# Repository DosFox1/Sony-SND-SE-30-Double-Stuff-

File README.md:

# Sony-SND-SE-30-Double-Stuff
BETA - A replacement for the Sony SND IC (part number 343-0045-A), specifically designed for the SE/30.
This design is a duplication of the previous Sony SND SMD version, but literally copied twice to fit two Sony SNDs onto the board without the DRC yelling at me.

# So What Is It?
This is quite literally the same design as before, with the same improvement of not needing the -12V rail. 
However, due to the board constraints of the SE/30, two of my SMD boards will not fit - at least easily. 
So this design just adds a second SND replacement so the DRC doesn't yell at me. 

It's all common jellybean parts, so nothing hyper specific is needed.

**Please note that -12V will need to be tapped from somewhere on the board, otherwise the audio doesn't work.**

**Also the 27R Pullup resistor at R11 on the logic board needs to be removed, otherwise POR doesn't work!**

The original SMD Design is here:
https://github.com/DosFox1/Sony-SND-SMT-Replacement

And the very original THT design is here:
https://github.com/DosFox1/Sony-SND-THT-Replacement

**Please Also Note That This Is Completely Untested, Build At Your Own Risk**

# Bill Of Materials:

```blocks
Part     Value          Device                       Package  Library                Sheet

C1       100n 16V       100N_CAP_0603                C0603    Capacitors SMD         1
C2       100n 16V       100N_CAP_0603                C0603    Capacitors SMD         1
C3       100n 16V       100N_CAP_0603                C0603    Capacitors SMD         1
C4       100n 16V       100N_CAP_0603                C0603    Capacitors SMD         1
C5       1u 16V         1U_CAP_0603                  C0603    Capacitors SMD         1
C6       100n 16V       100N_CAP_0603                C0603    Capacitors SMD         1
C7       470p           100P_CAP_0603                C0603    Capacitors SMD         1
C8       1n 50V         10N_CAP_0603                 C0603    Capacitors SMD         1
C9       100n 16V       100N_CAP_0603                C0603    Capacitors SMD         1
C10      100n 16V       100N_CAP_0603                C0603    Capacitors SMD         1
C11      220p           100P_CAP_0603                C0603    Capacitors SMD         1
C12      100n 16V       100N_CAP_0603                C0603    Capacitors SMD         1
C13      100n 16V       100N_CAP_0603                C0603    Capacitors SMD         1
C14      100n 16V       100N_CAP_0603                C0603    Capacitors SMD         1
C15      100n 16V       100N_CAP_0603                C0603    Capacitors SMD         1
C16      100n 16V       100N_CAP_0603                C0603    Capacitors SMD         1
C17      470p           100P_CAP_0603                C0603    Capacitors SMD         1
C18      1n 50V         10N_CAP_0603                 C0603    Capacitors SMD         1
C19      100n 16V       100N_CAP_0603                C0603    Capacitors SMD         1
C20      100n 16V       100N_CAP_0603                C0603    Capacitors SMD         1
C21      220p           100P_CAP_0603                C0603    Capacitors SMD         1
C22      100n 16V       100N_CAP_0603                C0603    Capacitors SMD         1
C23      1u 16V         1U_CAP_0603                  C0603    Capacitors SMD         1
C24      100n 16V       100N_CAP_0603                C0603    Capacitors SMD         1
D1       5.1V           DIODE-ZENER-MMSZ5232BS       SOD-123  SparkFun-DiscreteSemi  1
D2       5.1V           DIODE-ZENER-MMSZ5232BS       SOD-123  SparkFun-DiscreteSemi  1
IC1      TL072          OPAMP-DUALU                  SO08     SparkFun-IC-Amplifiers 1
IC2      4016D          4016D                        SO14     40xx                   1
IC3      NE555DRG4      555_SOIC8                    SOIC8    ICs                    1
IC4      74LVC1G06DBV   74LVC1G06DBV                 SOT23-5  74xx-little-us         1
IC5      Turned Pins    SND Turned Pins              DIP16    Pins                   1
IC6      4016D          4016D                        SO14     40xx                   1
IC7      Turned Pins    SND Turned Pins              DIP16    ICs                    1
IC8      74LVC1G06DBV   74LVC1G06DBV                 SOT23-5  74xx-little-us         1
IC9      NE555DRG4      555_SOIC8                    SOIC8    Pins                   1
IC10     TL072          OPAMP-DUALU                  SO08     SparkFun-IC-Amplifiers 1
Q1       MMBT3906       TRANS_PNP-PMBT3906|MMBT3906L SOT23-3  SparkFun-DiscreteSemi  1
Q2       MMBT3904       TRANS_NPN-MMBT2222AL         SOT23-3  SparkFun-DiscreteSemi  1
Q3       MMBT3906       TRANS_PNP-PMBT3906|MMBT3906L SOT23-3  SparkFun-DiscreteSemi  1
Q4       MMBT3904       TRANS_NPN-MMBT2222AL         SOT23-3  SparkFun-DiscreteSemi  1
R1       1M             GENERIC_RESISTOR_0603        R0603    Resistors SMD          1
R2       1M             GENERIC_RESISTOR_0603        R0603    Resistors SMD          1
R3       6K8            GENERIC_RESISTOR_0603        R0603    Resistors SMD          1
R4       47K            47K_RESISTOR                 R0603    Resistors SMD          1
R5       1k             1K_RESISTOR_0603             R0603    Resistors SMD          1
R6       47K            47K_RESISTOR                 R0603    Resistors SMD          1
R7       68K            GENERIC_RESISTOR_0603        R0603    Resistors SMD          1
R8       150K           GENERIC_RESISTOR_0603        R0603    Resistors SMD          1
R9       470K           GENERIC_RESISTOR_0603        R0603    Resistors SMD          1
R10      470K           GENERIC_RESISTOR_0603        R0603    Resistors SMD          1
R11      200K           GENERIC_RESISTOR_0603        R0603    Resistors SMD          1
R12      150R           150R_RESISTOR_0603           R0603    Resistors SMD          1
R13      47K            47K_RESISTOR                 R0603    Resistors SMD          1
R14      47K            47K_RESISTOR                 R0603    Resistors SMD          1
R15      1M             GENERIC_RESISTOR_0603        R0603    Resistors SMD          1
R16      1M             GENERIC_RESISTOR_0603        R0603    Resistors SMD          1
R17      1k             1K_RESISTOR_0603             R0603    Resistors SMD          1
R18      6K8            GENERIC_RESISTOR_0603        R0603    Resistors SMD          1
R19      68K            GENERIC_RESISTOR_0603        R0603    Resistors SMD          1
R20      150K           GENERIC_RESISTOR_0603        R0603    Resistors SMD          1
R21      470K           GENERIC_RESISTOR_0603        R0603    Resistors SMD          1
R22      470K           GENERIC_RESISTOR_0603        R0603    Resistors SMD          1
R23      200K           GENERIC_RESISTOR_0603        R0603    Resistors SMD          1
R24      150R           150R_RESISTOR_0603           R0603    Resistors SMD          1

```

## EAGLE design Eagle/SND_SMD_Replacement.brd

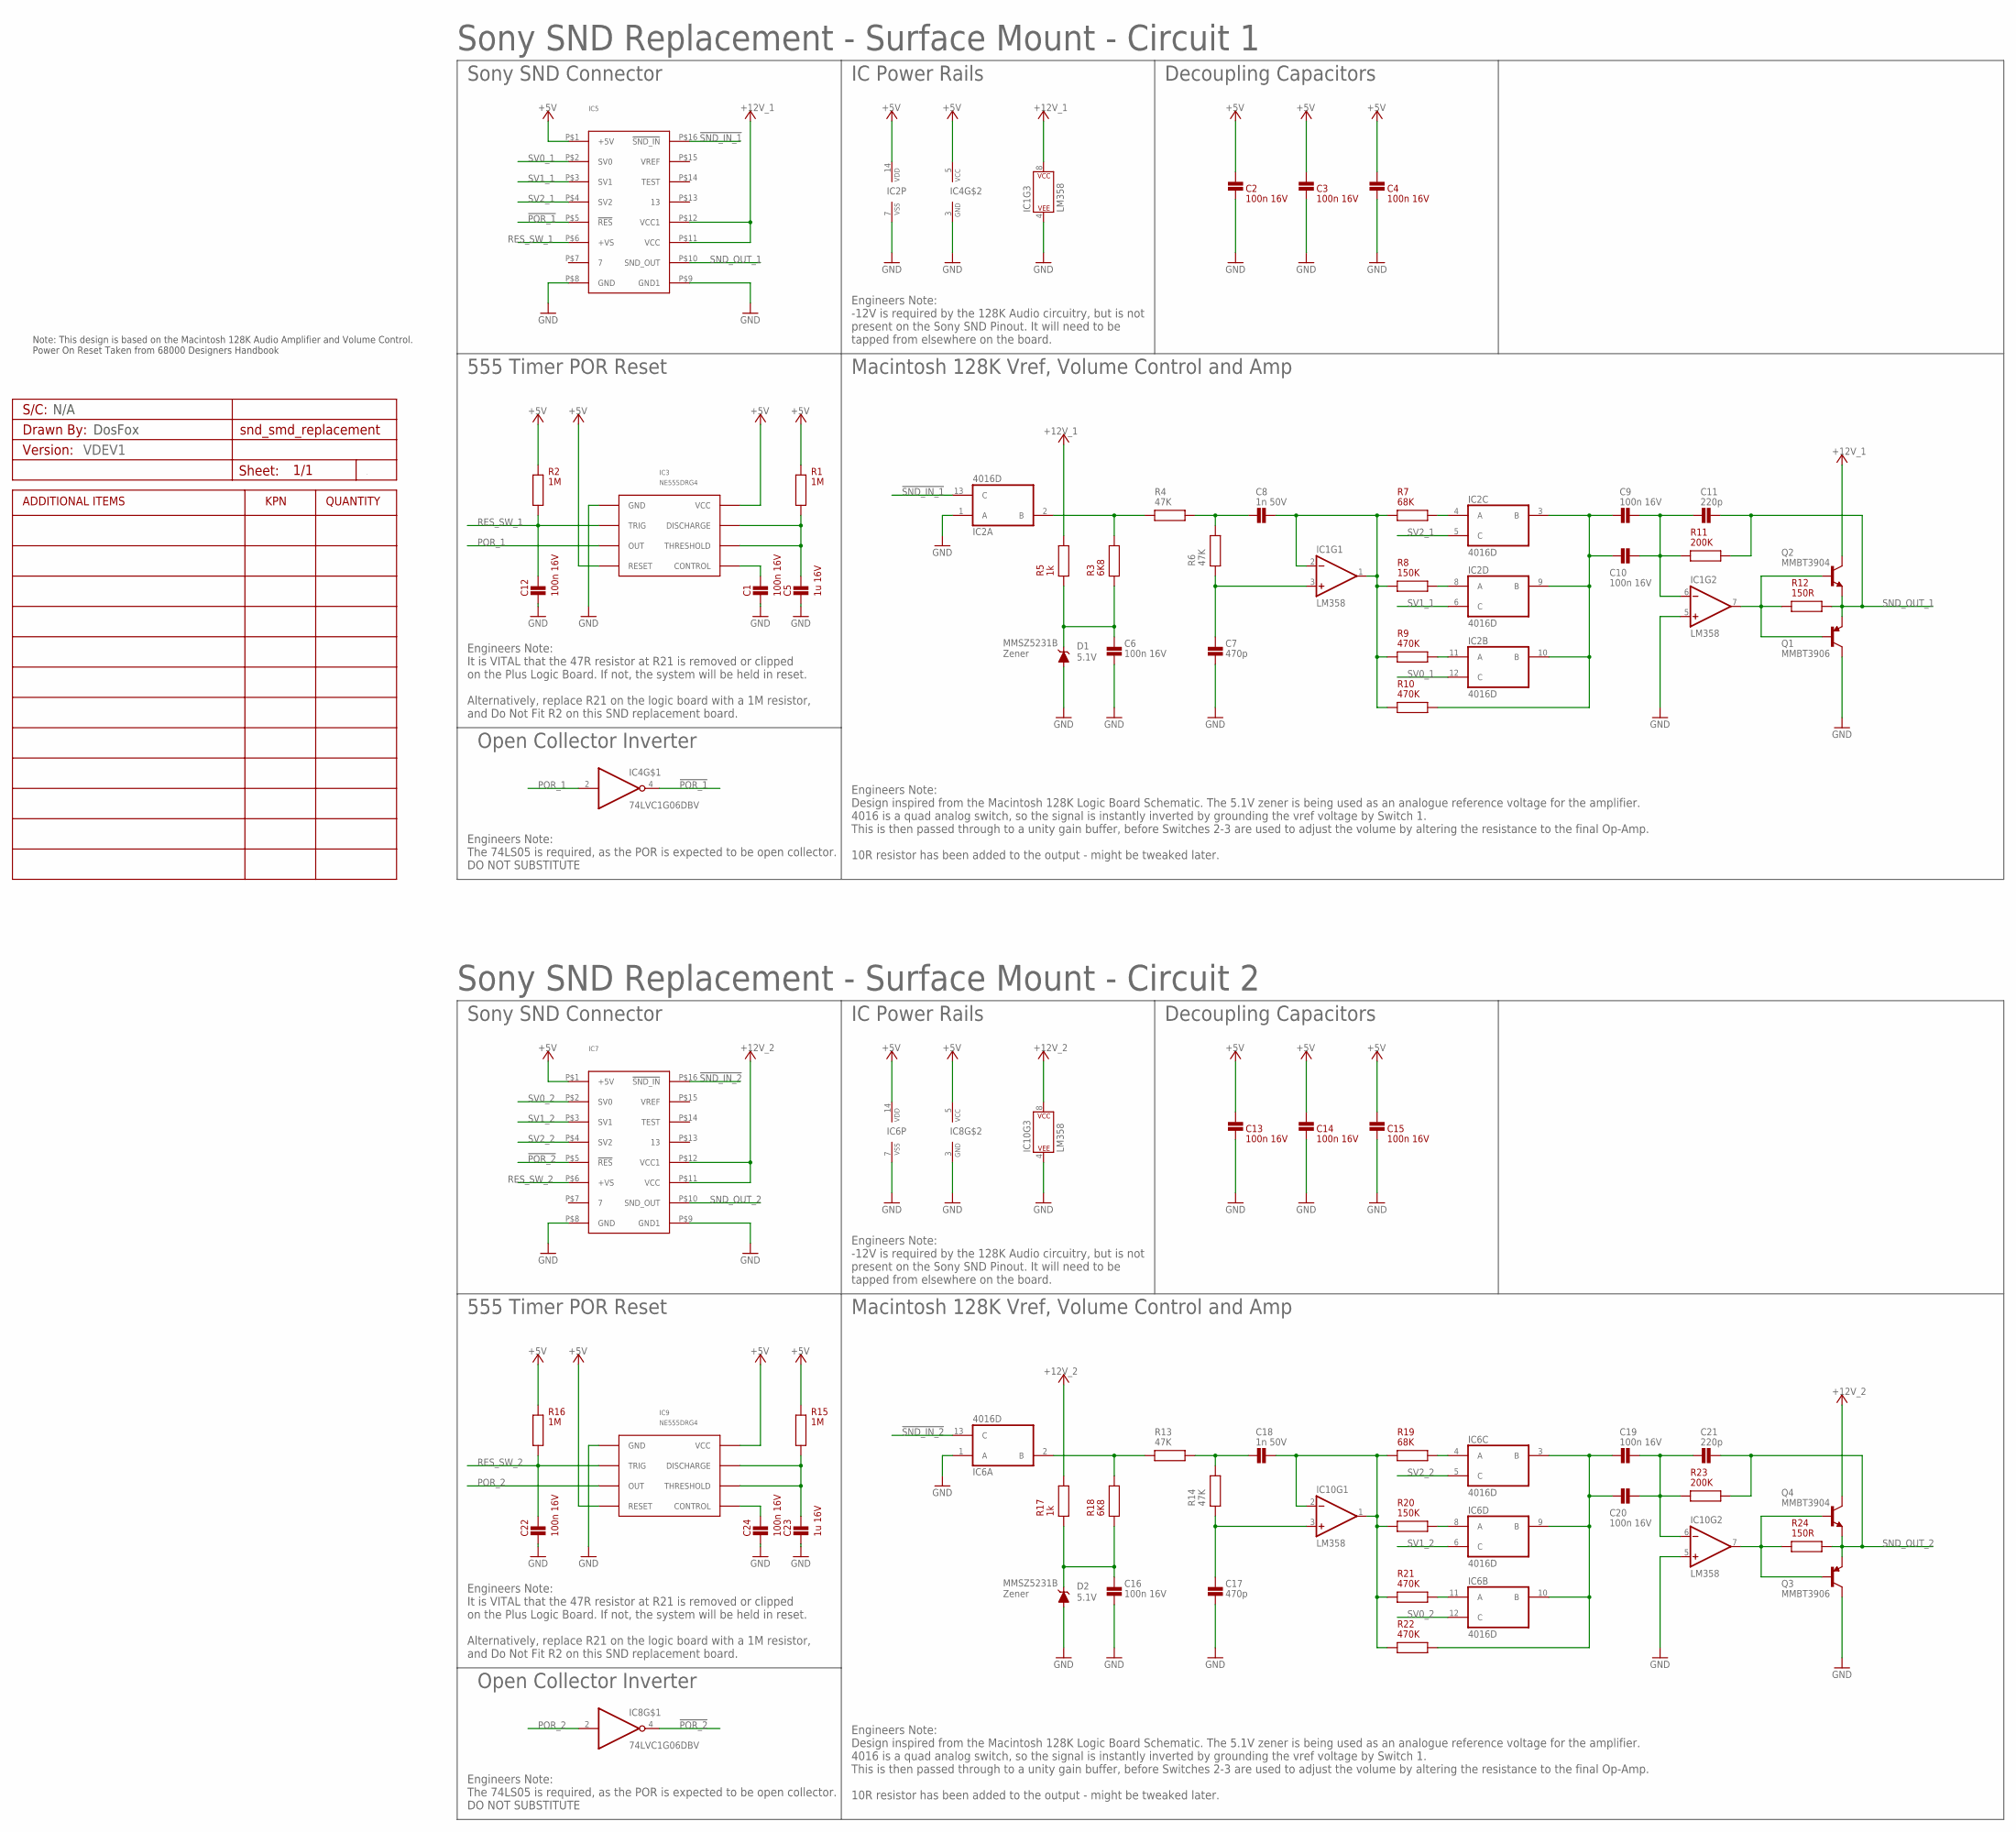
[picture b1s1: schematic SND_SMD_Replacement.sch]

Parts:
A1: VDEV1; PCB_CUSTOM_DETAILS
C1, C2, C3, C4, C6, C9, C10, C12, C13, C14, C15, C16, C19, C20, C22, C24: 100n 16V; C0603
C5, C23: 1u 16V; C0603
C7, C17: 470p; C0603
C8, C18: 1n 50V; C0603
C11, C21: 220p; C0603
D1, D2: 5.1V; SOD-323
IC1, IC10: LM358; SO08
IC2, IC6: 4016D; SO14
IC3, IC9: NE555DRG4; SOIC8
IC4, IC8: 74LVC1G06DBV; SOT23-5
IC5, IC7: SND; DIP16
Q1, Q3: MMBT3906; SOT23-3
Q2, Q4: MMBT3904; SOT23-3
R1, R2, R15, R16: 1M; R0603
R3, R18: 6K8; R0603
R4, R6, R13, R14: 47K; R0603
R5, R17: 1k; R0603
R7, R19: 68K; R0603
R8, R20: 150K; R0603
R9, R10, R21, R22: 470K; R0603
R11, R23: 200K; R0603
R12, R24: 150R; R0603

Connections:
!POR_1: IC4.4 (O), IC5.P$5 (!RES)
!POR_2: IC7.P$5 (!RES), IC8.4 (O)
!SND_IN_1: IC2.13 (C), IC5.P$16 (!SND_IN)
!SND_IN_2: IC6.13 (C), IC7.P$16 (!SND_IN)
+5V: C2.2, C3.2, C4.2, C13.2, C14.2, C15.2, IC2.14 (VDD), IC3.P$4 (RESET), IC3.P$8 (VCC), IC4.5 (VCC), IC5.P$1 (+5V), IC6.14 (VDD), IC7.P$1 (+5V), IC8.5 (VCC), IC9.P$4 (RESET), IC9.P$8 (VCC), R1.2, R2.2, R15.2, R16.2
+12V_1: IC1.8 (P$V+), IC5.P$11 (VCC), IC5.P$12 (VCC1), Q2.3 (C), R5.2
+12V_2: IC7.P$11 (VCC), IC7.P$12 (VCC1), IC10.8 (P$V+), Q4.3 (C), R17.2
GND: C1.1, C2.1, C3.1, C4.1, C5.1, C6.1, C7.1, C12.1, C13.1, C14.1, C15.1, C16.1, C17.1, C22.1, C23.1, C24.1, D1.A, D2.A, IC1.4 (P$V-), IC1.5 (+IN), IC2.1 (A), IC2.7 (VSS), IC3.P$1 (GND), IC4.3 (GND), IC5.P$8 (GND), IC5.P$9 (GND1), IC6.1 (A), IC6.7 (VSS), IC7.P$8 (GND), IC7.P$9 (GND1), IC8.3 (GND), IC9.P$1 (GND), IC10.4 (P$V-), IC10.5 (+IN), Q1.3 (C), Q3.3 (C)
unnamed: IC2.2 (B), R3.2, R4.1
unnamed: C19.1, C20.1, IC6.3 (B), IC6.9 (B), IC6.10 (B), R22.2
unnamed: C9.1, C10.1, IC2.3 (B), IC2.9 (B), IC2.10 (B), R10.2
unnamed: C8.1, R4.2, R6.2
unnamed: C6.2, D1.C, R3.1, R5.1
unnamed: C7.2, IC1.3 (+IN), R6.1
unnamed: IC2.4 (A), R7.2
unnamed: IC2.8 (A), R8.2
unnamed: IC2.11 (A), R9.2
unnamed: C9.2, C10.2, C11.1, IC1.6 (-IN), R11.1
unnamed: C5.2, IC3.P$6 (THRESHOLD), IC3.P$7 (DISCHARGE), R1.1
unnamed: C8.2, IC1.1 (OUT), IC1.2 (-IN), R7.1, R8.1, R9.1, R10.1
unnamed: IC6.2 (B), R13.1, R18.2
unnamed: C18.1, R13.2, R14.2
unnamed: IC1.7 (OUT), Q1.1 (B), Q2.1 (B), R12.1
unnamed: C16.2, D2.C, R17.1, R18.1
unnamed: C1.2, IC3.P$5 (CONTROL)
unnamed: C17.2, IC10.3 (+IN), R14.1
unnamed: IC6.4 (A), R19.2
unnamed: IC6.8 (A), R20.2
unnamed: IC6.11 (A), R21.2
unnamed: C19.2, C20.2, C21.1, IC10.6 (-IN), R23.1
unnamed: IC10.7 (OUT), Q3.1 (B), Q4.1 (B), R24.1
unnamed: C18.2, IC10.1 (OUT), IC10.2 (-IN), R19.1, R20.1, R21.1, R22.1
unnamed: C23.2, IC9.P$6 (THRESHOLD), IC9.P$7 (DISCHARGE), R15.1
unnamed: C24.2, IC9.P$5 (CONTROL)
POR_1: IC3.P$3 (OUT), IC4.2 (I)
POR_2: IC8.2 (I), IC9.P$3 (OUT)
RES_SW_1: C12.2, IC3.P$2 (TRIG), IC5.P$6 (+VS), R2.1
RES_SW_2: C22.2, IC7.P$6 (+VS), IC9.P$2 (TRIG), R16.1
SND_OUT_1: C11.2, IC5.P$10 (SND_OUT), Q1.2 (E), Q2.2 (E), R11.2, R12.2
SND_OUT_2: C21.2, IC7.P$10 (SND_OUT), Q3.2 (E), Q4.2 (E), R23.2, R24.2
SV0_1: IC2.12 (C), IC5.P$2 (SV0)
SV0_2: IC6.12 (C), IC7.P$2 (SV0)
SV1_1: IC2.6 (C), IC5.P$3 (SV1)
SV1_2: IC6.6 (C), IC7.P$3 (SV1)
SV2_1: IC2.5 (C), IC5.P$4 (SV2)
SV2_2: IC6.5 (C), IC7.P$4 (SV2)

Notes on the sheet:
Note: This design is based on the Macintosh 128K Audio Amplifier and Volume Control. Power On Reset Taken from 68000 Designers Handbook
DosFox
N/A
MMSZ5231B Zener
Sony SND Replacement - Surface Mount - Circuit 1
Sony SND Connector
IC Power Rails
Decoupling Capacitors
555 Timer POR Reset
Open Collector Inverter
Macintosh 128K Vref, Volume Control and Amp
Engineers Note: Design inspired from the Macintosh 128K Logic Board Schematic. The 5.1V zener is being used as an analogue reference voltage for the amplifier. 4016 is a quad analog switch, so the signal is instantly inverted by grounding the vref voltage by Switch 1. This is then passed through to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
Engineers Note: It is VITAL that the 47R resistor at R21 is removed or clipped on the Plus Logic Board. If not, the system will be held in reset. Alternatively, replace R21 on the logic board with a 1M resistor, and Do Not Fit R2 on this SND replacement board.
Engineers Note: The 74LS05 is required, as the POR is expected to be open collector. DO NOT SUBSTITUTE
Engineers Note: -12V is required by the 128K Audio circuitry, but is not present on the Sony SND Pinout. It will need to be tapped from elsewhere on the board.
Sony SND Replacement - Surface Mount - Circuit 2

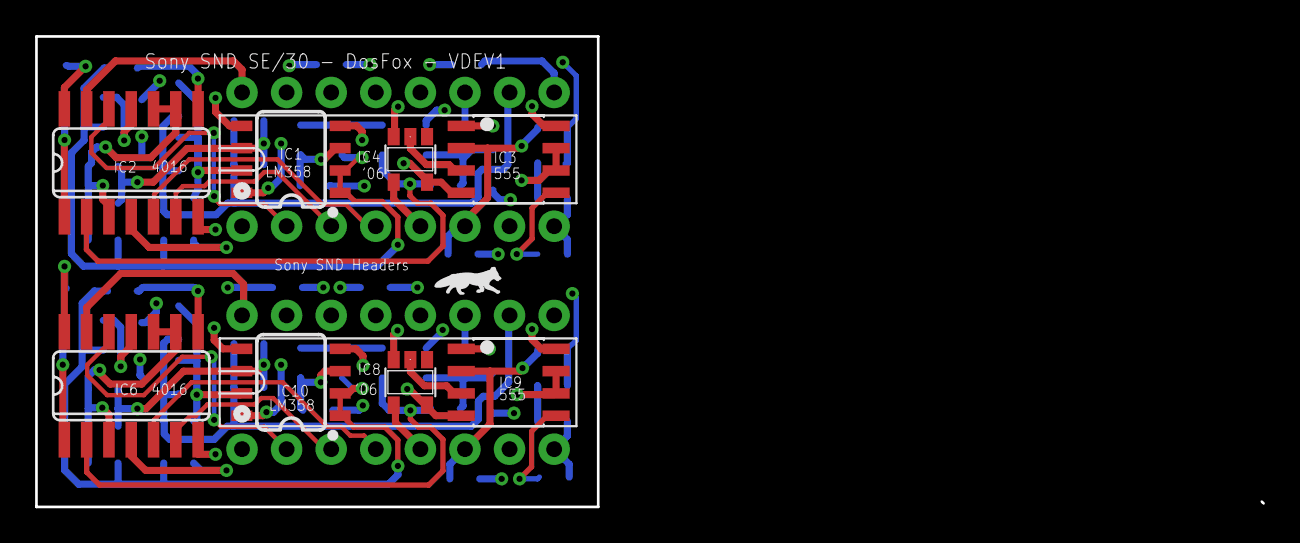
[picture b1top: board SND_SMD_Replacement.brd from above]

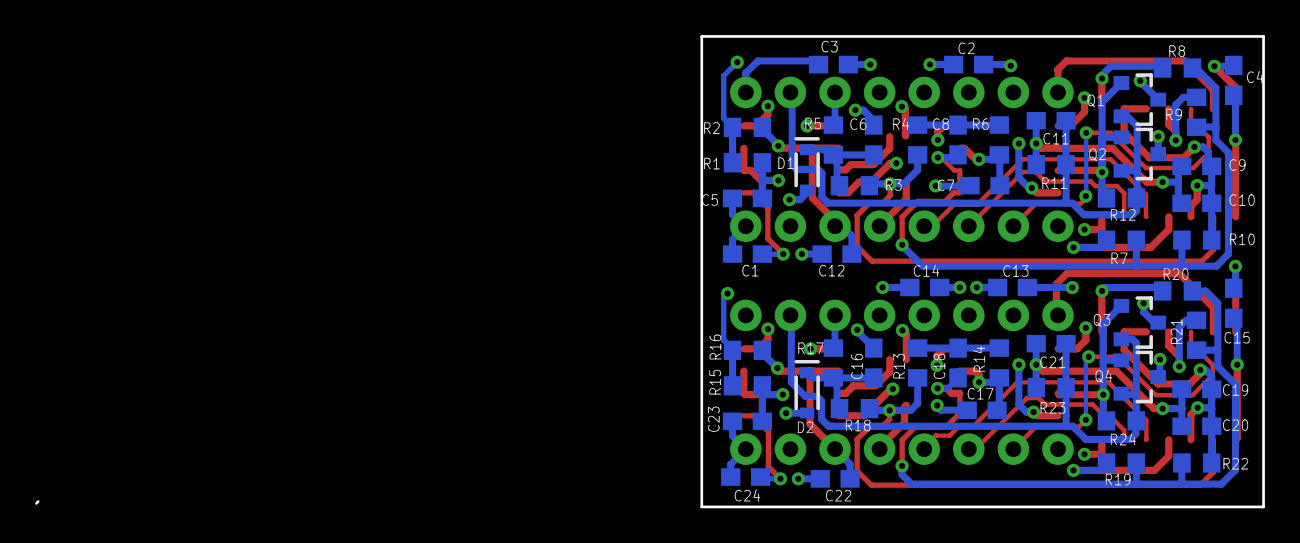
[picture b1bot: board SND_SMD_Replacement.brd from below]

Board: 4 copper layers, 69.9 x 26.8 mm, 65 parts (54 on the bottom side), 46 nets.

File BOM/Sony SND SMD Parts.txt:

Partlist

Exported from SND_SMD_Replacement.sch at 31/Oct/24 13:54

EAGLE Version 9.6.2 Copyright (c) 1988-2020 Autodesk, Inc.

Assembly variant: 

Part     Value          Device                       Package  Library                Sheet

C1       100n 16V       100N_CAP_0603                C0603    Capacitors SMD         1
C2       100n 16V       100N_CAP_0603                C0603    Capacitors SMD         1
C3       100n 16V       100N_CAP_0603                C0603    Capacitors SMD         1
C4       100n 16V       100N_CAP_0603                C0603    Capacitors SMD         1
C5       1u 16V         1U_CAP_0603                  C0603    Capacitors SMD         1
C6       100n 16V       100N_CAP_0603                C0603    Capacitors SMD         1
C7       470p           100P_CAP_0603                C0603    Capacitors SMD         1
C8       1n 50V         10N_CAP_0603                 C0603    Capacitors SMD         1
C9       100n 16V       100N_CAP_0603                C0603    Capacitors SMD         1
C10      100n 16V       100N_CAP_0603                C0603    Capacitors SMD         1
C11      220p           100P_CAP_0603                C0603    Capacitors SMD         1
C12      100n 16V       100N_CAP_0603                C0603    Capacitors SMD         1
C13      100n 16V       100N_CAP_0603                C0603    Capacitors SMD         1
C14      100n 16V       100N_CAP_0603                C0603    Capacitors SMD         1
C15      100n 16V       100N_CAP_0603                C0603    Capacitors SMD         1
C16      100n 16V       100N_CAP_0603                C0603    Capacitors SMD         1
C17      470p           100P_CAP_0603                C0603    Capacitors SMD         1
C18      1n 50V         10N_CAP_0603                 C0603    Capacitors SMD         1
C19      100n 16V       100N_CAP_0603                C0603    Capacitors SMD         1
C20      100n 16V       100N_CAP_0603                C0603    Capacitors SMD         1
C21      220p           100P_CAP_0603                C0603    Capacitors SMD         1
C22      100n 16V       100N_CAP_0603                C0603    Capacitors SMD         1
C23      1u 16V         1U_CAP_0603                  C0603    Capacitors SMD         1
C24      100n 16V       100N_CAP_0603                C0603    Capacitors SMD         1
D1       5.1V           DIODE-ZENER-MMSZ5232BS       SOD-323  SparkFun-DiscreteSemi  1
D2       5.1V           DIODE-ZENER-MMSZ5232BS       SOD-323  SparkFun-DiscreteSemi  1
IC1      LM358          OPAMP-DUALU                  SO08     SparkFun-IC-Amplifiers 1
IC2      4016D          4016D                        SO14     40xx                   1
IC3      NE555DRG4      555_SOIC8                    SOIC8    ICs                    1
IC4      74LVC1G06DBV   74LVC1G06DBV                 SOT23-5  74xx-little-us         1
IC5      Turned Pins    SND Turned Pins              DIP16    Pins                   1
IC6      4016D          4016D                        SO14     40xx                   1
IC7      Turned Pins    SND Turned Pins              DIP16    ICs                    1
IC8      74LVC1G06DBV   74LVC1G06DBV                 SOT23-5  74xx-little-us         1
IC9      NE555DRG4      555_SOIC8                    SOIC8    Pins                   1
IC10     LM358          OPAMP-DUALU                  SO08     SparkFun-IC-Amplifiers 1
Q1       MMBT3906       TRANS_PNP-PMBT3906|MMBT3906L SOT23-3  SparkFun-DiscreteSemi  1
Q2       MMBT3904       TRANS_NPN-MMBT2222AL         SOT23-3  SparkFun-DiscreteSemi  1
Q3       MMBT3906       TRANS_PNP-PMBT3906|MMBT3906L SOT23-3  SparkFun-DiscreteSemi  1
Q4       MMBT3904       TRANS_NPN-MMBT2222AL         SOT23-3  SparkFun-DiscreteSemi  1
R1       1M             GENERIC_RESISTOR_0603        R0603    Resistors SMD          1
R2       1M             GENERIC_RESISTOR_0603        R0603    Resistors SMD          1
R3       6K8            GENERIC_RESISTOR_0603        R0603    Resistors SMD          1
R4       47K            47K_RESISTOR                 R0603    Resistors SMD          1
R5       1k             1K_RESISTOR_0603             R0603    Resistors SMD          1
R6       47K            47K_RESISTOR                 R0603    Resistors SMD          1
R7       68K            GENERIC_RESISTOR_0603        R0603    Resistors SMD          1
R8       150K           GENERIC_RESISTOR_0603        R0603    Resistors SMD          1
R9       470K           GENERIC_RESISTOR_0603        R0603    Resistors SMD          1
R10      470K           GENERIC_RESISTOR_0603        R0603    Resistors SMD          1
R11      200K           GENERIC_RESISTOR_0603        R0603    Resistors SMD          1
R12      150R           150R_RESISTOR_0603           R0603    Resistors SMD          1
R13      47K            47K_RESISTOR                 R0603    Resistors SMD          1
R14      47K            47K_RESISTOR                 R0603    Resistors SMD          1
R15      1M             GENERIC_RESISTOR_0603        R0603    Resistors SMD          1
R16      1M             GENERIC_RESISTOR_0603        R0603    Resistors SMD          1
R17      1k             1K_RESISTOR_0603             R0603    Resistors SMD          1
R18      6K8            GENERIC_RESISTOR_0603        R0603    Resistors SMD          1
R19      68K            GENERIC_RESISTOR_0603        R0603    Resistors SMD          1
R20      150K           GENERIC_RESISTOR_0603        R0603    Resistors SMD          1
R21      470K           GENERIC_RESISTOR_0603        R0603    Resistors SMD          1
R22      470K           GENERIC_RESISTOR_0603        R0603    Resistors SMD          1
R23      200K           GENERIC_RESISTOR_0603        R0603    Resistors SMD          1
R24      150R           150R_RESISTOR_0603           R0603    Resistors SMD          1

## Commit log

2024-11-25 Add files via upload
    Initial commit of the files for the Double Stuff Sony SND board
2024-11-25 Update README.md
    updated README to some semblance of a sane commit
2024-11-29 Add files via upload
    Oops. Gerber export was set to two layers - not four.
2024-12-02 Add files via upload
    Regenerated Gerbers using Kicad instead of Eagle. Eagle appears to have issues with four layer boards.
2025-08-29 Update README.md
    updated for VDEV2
2025-08-29 Added VDEV2 (hopefully working)
2025-08-29 Update README for VDEV2

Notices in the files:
parts and their libraries:
SparkFun-DiscreteSemi: Licensing: Creative Commons ShareAlike 4.0 International - https://creativecommons.org/licenses/by-sa/4.0
